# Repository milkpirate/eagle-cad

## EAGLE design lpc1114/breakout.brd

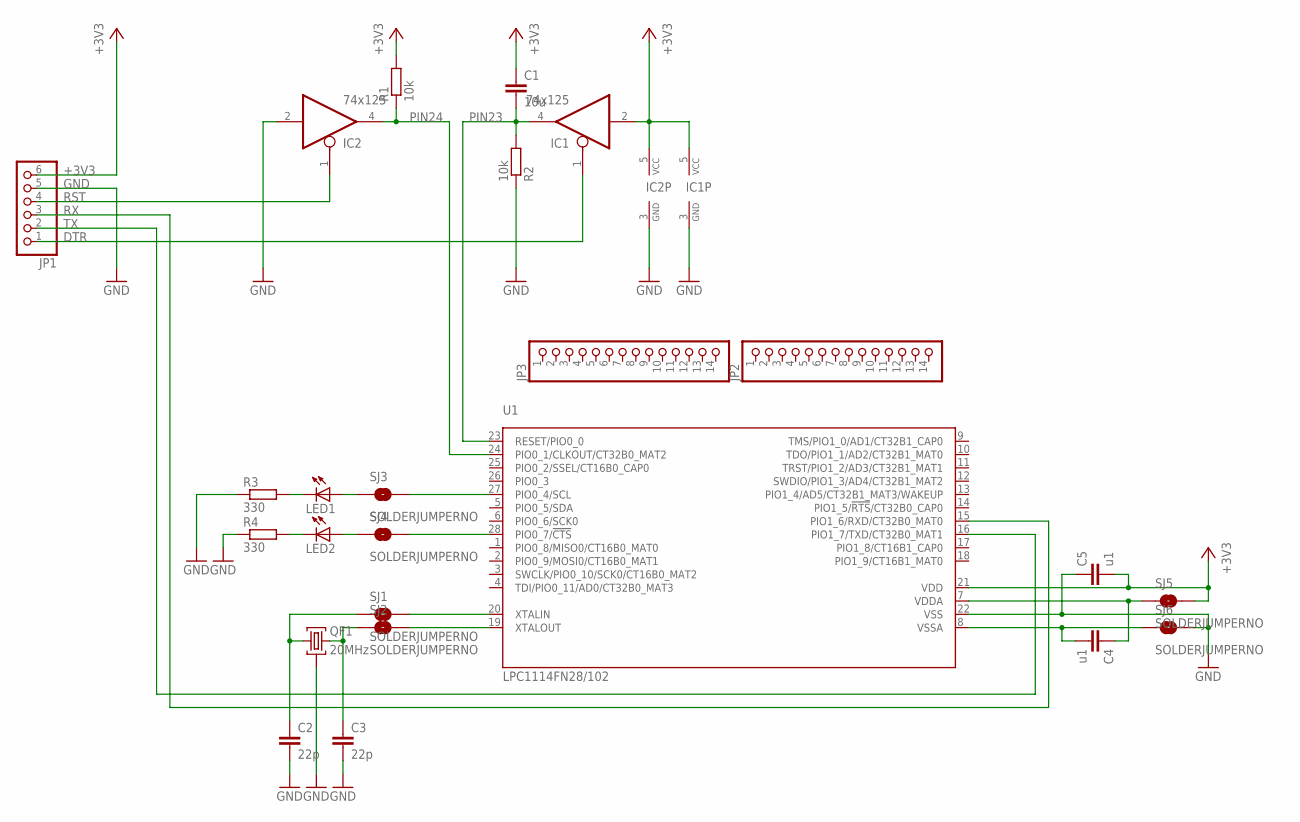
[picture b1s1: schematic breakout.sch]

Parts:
C1: 10u; C0805K
C2, C3: 22p; C0805K
C4, C5: u1; C0805K
IC1, IC2: 74x125; SOT23-5
JP1: PINHD-1X6/90; 1X06/90
JP2, JP3: PINHD-1X14; 1X14
LED1, LED2: LEDLD260; LD260
QF1: 20MHz; HC49U
R1, R2: 10k; M0805
R3, R4: 330; M0805
SJ1, SJ2, SJ3, SJ4, SJ5, SJ6: SOLDERJUMPERNO; SJ_2S-NO
U1: LPC1114FN28/102; SOT117

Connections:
+3V3: C1.1, C5.2, IC1.2 (I), IC1.5 (VCC), IC2.5 (VCC), JP1.6, R1.2, SJ5.2, U1.21 (VDD)
DTR: IC1.1 (OE), JP1.1
GND: C2.2, C3.2, C5.1, IC1.3 (GND), IC2.2 (I), IC2.3 (GND), JP1.5, QF1.2, R2.1, R3.1, R4.1, SJ6.2, U1.22 (VSS)
unnamed: LED2.A, SJ4.1
unnamed: LED1.A, SJ3.1
unnamed: LED1.K (C), R3.2
unnamed: LED2.K (C), R4.2
unnamed: SJ2.2, U1.19 (XTALOUT)
unnamed: SJ1.2, U1.20 (XTALIN)
unnamed: SJ4.2, U1.28 (PIO0_7/!CTS!)
unnamed: SJ3.2, U1.27 (PIO0_4/SCL)
unnamed: C3.1, QF1.3, SJ2.1
unnamed: C2.1, QF1.1, SJ1.1
PIN7: C4.1, SJ5.1, U1.7 (VDDA)
PIN8: C4.2, SJ6.1, U1.8 (VSSA)
PIN23: C1.2, IC1.4 (O), R2.2, U1.23 (RESET/PIO0_0)
PIN24: IC2.4 (O), R1.1, U1.24 (PIO0_1/CLKOUT/CT32B0_MAT2)
RST: IC2.1 (OE), JP1.4
RX: JP1.3, U1.15 (PIO1_6/RXD/CT32B0_MAT0)
TX: JP1.2, U1.16 (PIO1_7/TXD/CT32B0_MAT1)

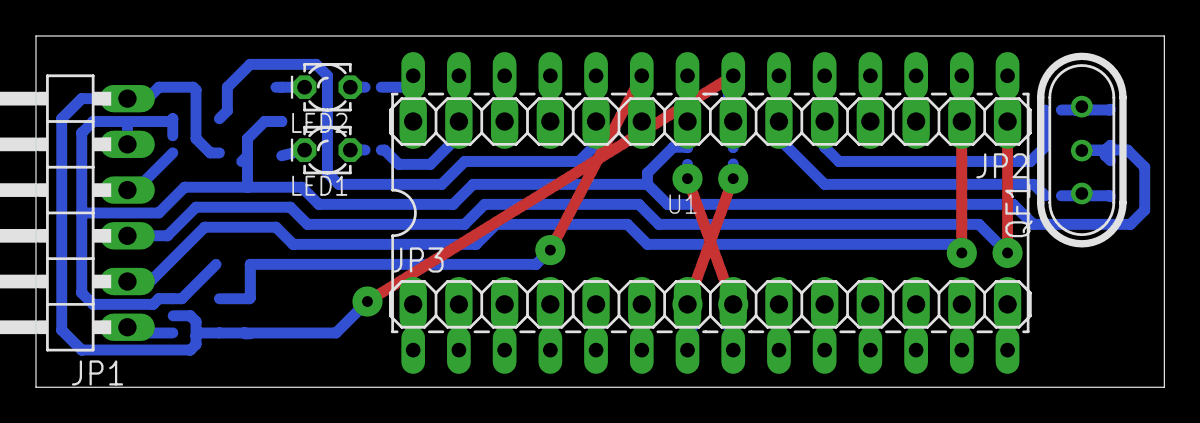
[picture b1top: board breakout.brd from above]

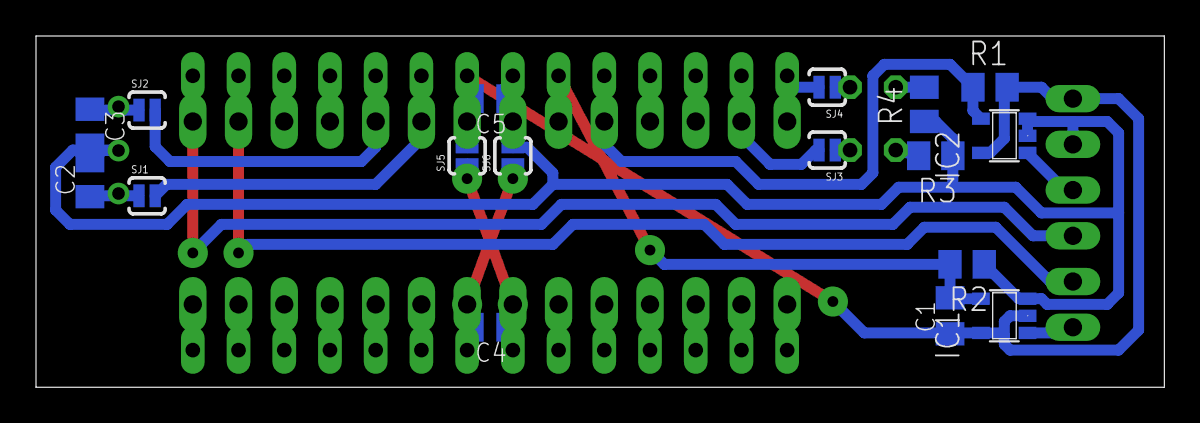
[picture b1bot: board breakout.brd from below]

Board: 2 copper layers, 62.7 x 19.5 mm, 24 parts (17 on the bottom side), 20 nets.

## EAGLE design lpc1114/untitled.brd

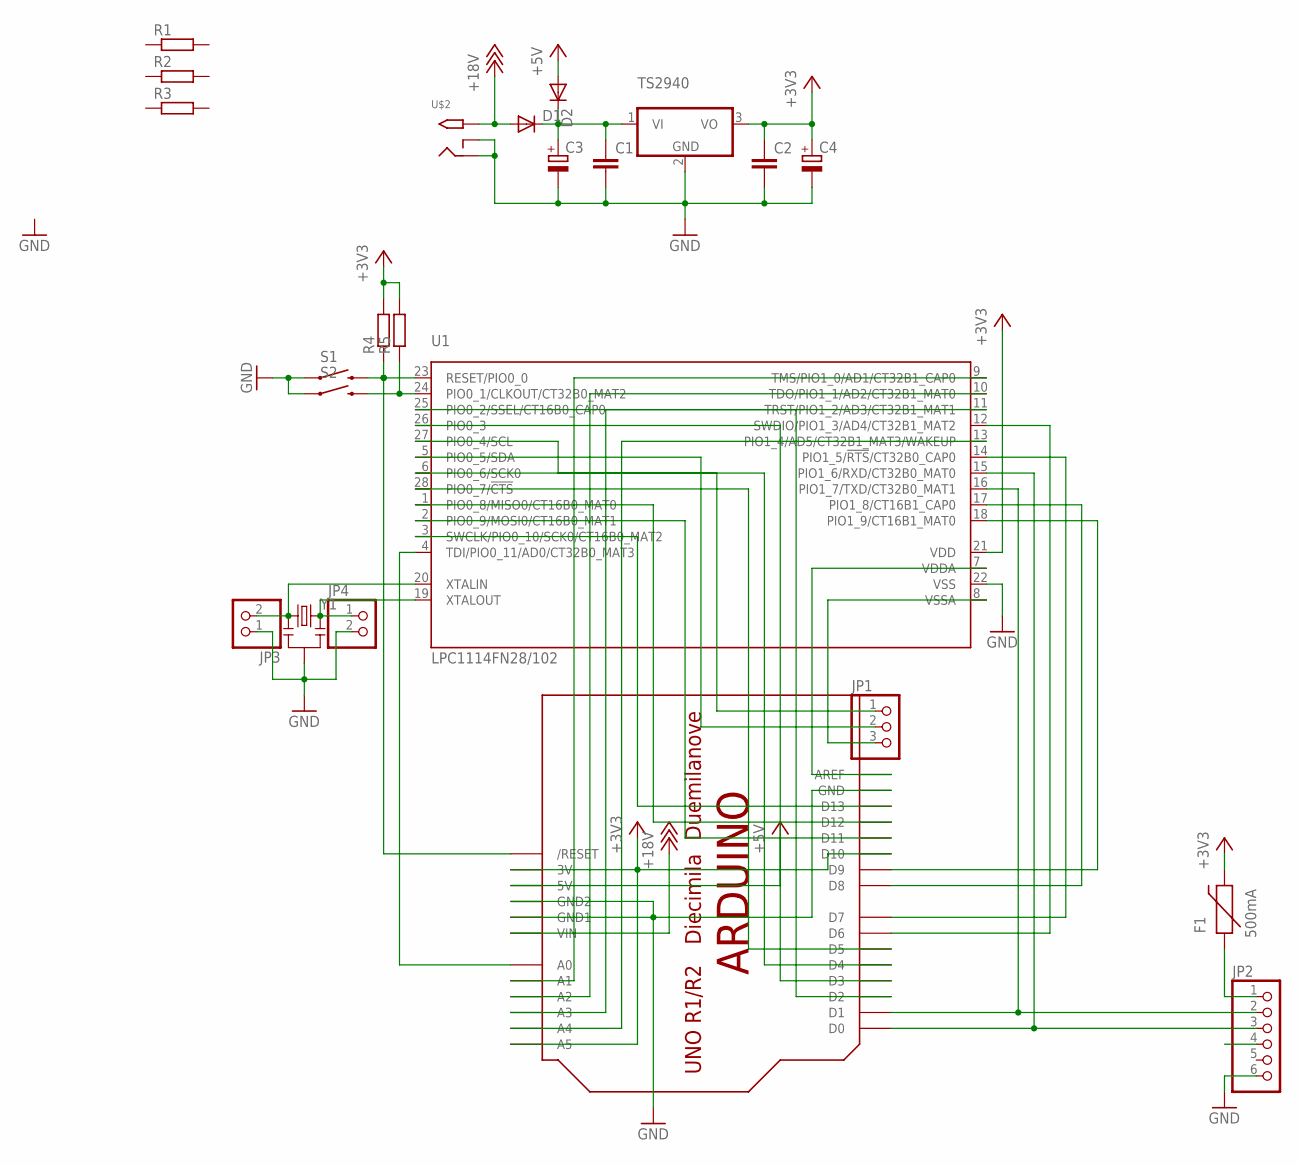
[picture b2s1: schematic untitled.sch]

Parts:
C1, C2: C-EU025-025X050; C025-025X050
C3, C4: CPOL-EUE2.5-6; E2,5-6
D1, D2: DIODE-C1702-05; C1702-05
F1: 500mA; PTC
JP1: PINHD-1X3; 1X03
JP2: PINHD-1X6/90; 1X06/90
JP3, JP4: PINHD-1X2; 1X02
R1, R2, R3, R4, R5: R-EU_0204/7; 0204/7
S1, S2: SWITCH-MOMENTARY-2PTH; TACTILE-PTH
TS2940: 7805T; TO220H
U1: LPC1114FN28/102; SOT117
U$1: ARDUINO-BPLACE
U$2: 2.1MMJACKTHM; PJ-102A
Y1: RESONATORPTH; RESONATOR-PTH

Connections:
+3V3: C2.1, C4.+, F1.P$2 (2), R4.2, R5.2, TS2940.3 (VO), U1.21 (VDD), U$1.3V, U$1.A5, U$1.D10
+5V: D2.A, U$1.5V
+18V: D1.A, U$1.VIN, U$2.TIP
GND: C1.2, C2.2, C3.-, C4.-, JP2.6, JP3.1, JP4.2, S1.1, S2.1, TS2940.2 (GND), U1.22 (VSS), U$1.GND, U$1.GND1, U$1.GND2, U$2.RING, U$2.RING_SW, Y1.2
unnamed: JP2.2, U1.16 (PIO1_7/TXD/CT32B0_MAT1), U$1.D1
unnamed: U1.4 (TDI/PIO0_11/AD0/CT32B0_MAT3), U$1.A0
unnamed: U1.9 (TMS/PIO1_0/AD1/CT32B1_CAP0), U$1.A1
unnamed: U1.10 (TDO/PIO1_1/AD2/CT32B1_MAT0), U$1.A2
unnamed: U1.11 (TRST/PIO1_2/AD3/CT32B1_MAT1), U$1.A3
unnamed: U1.13 (PIO1_4/AD5/CT32B1_MAT3/WAKEUP), U$1.A4
unnamed: C1.1, C3.+, D1.C, D2.C, TS2940.1 (VI)
unnamed: R4.1, S1.3 (2), U1.23 (RESET/PIO0_0), U$1.RESET (/RESET)
unnamed: U1.7 (VDDA), U$1.AREF
unnamed: JP1.3, U1.8 (VSSA)
unnamed: F1.P$1 (1), JP2.1
unnamed: U1.3 (SWCLK/PIO0_10/SCK0/CT16B0_MAT2), U$1.D13
unnamed: U1.2 (PIO0_9/MOSI0/CT16B0_MAT1), U$1.D11
unnamed: JP2.3, U1.15 (PIO1_6/RXD/CT32B0_MAT0), U$1.D0
unnamed: U1.1 (PIO0_8/MISO0/CT16B0_MAT0), U$1.D12
unnamed: JP1.2, U1.5 (PIO0_5/SDA)
unnamed: JP1.1, U1.27 (PIO0_4/SCL)
unnamed: R5.1, S2.3 (2), U1.24 (PIO0_1/CLKOUT/CT32B0_MAT2)
unnamed: JP3.2, U1.20 (XTALIN), Y1.1
unnamed: JP4.1, U1.19 (XTALOUT), Y1.3
unnamed: U1.25 (PIO0_2/SSEL/CT16B0_CAP0), U$1.D2
unnamed: U1.26 (PIO0_3), U$1.D3
unnamed: U1.6 (PIO0_6/SCK0), U$1.D4
unnamed: U1.28 (PIO0_7/!CTS!), U$1.D5
unnamed: U1.12 (SWDIO/PIO1_3/AD4/CT32B1_MAT2), U$1.D6
unnamed: U1.14 (PIO1_5/!RTS!/CT32B0_CAP0), U$1.D7
unnamed: U1.17 (PIO1_8/CT16B1_CAP0), U$1.D8
unnamed: U1.18 (PIO1_9/CT16B1_MAT0), U$1.D9

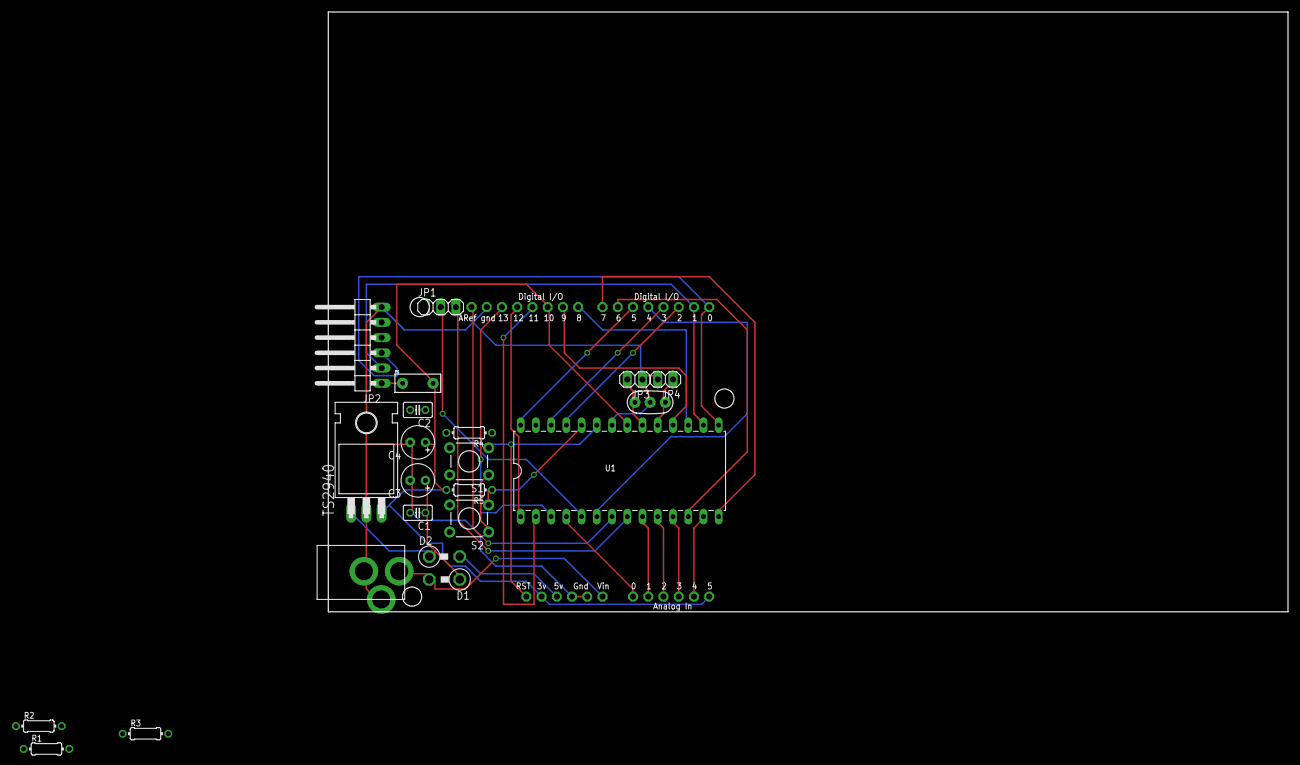
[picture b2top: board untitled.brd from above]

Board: 2 copper layers, 160.0 x 100.0 mm, 23 parts (0 on the bottom side), 32 nets.

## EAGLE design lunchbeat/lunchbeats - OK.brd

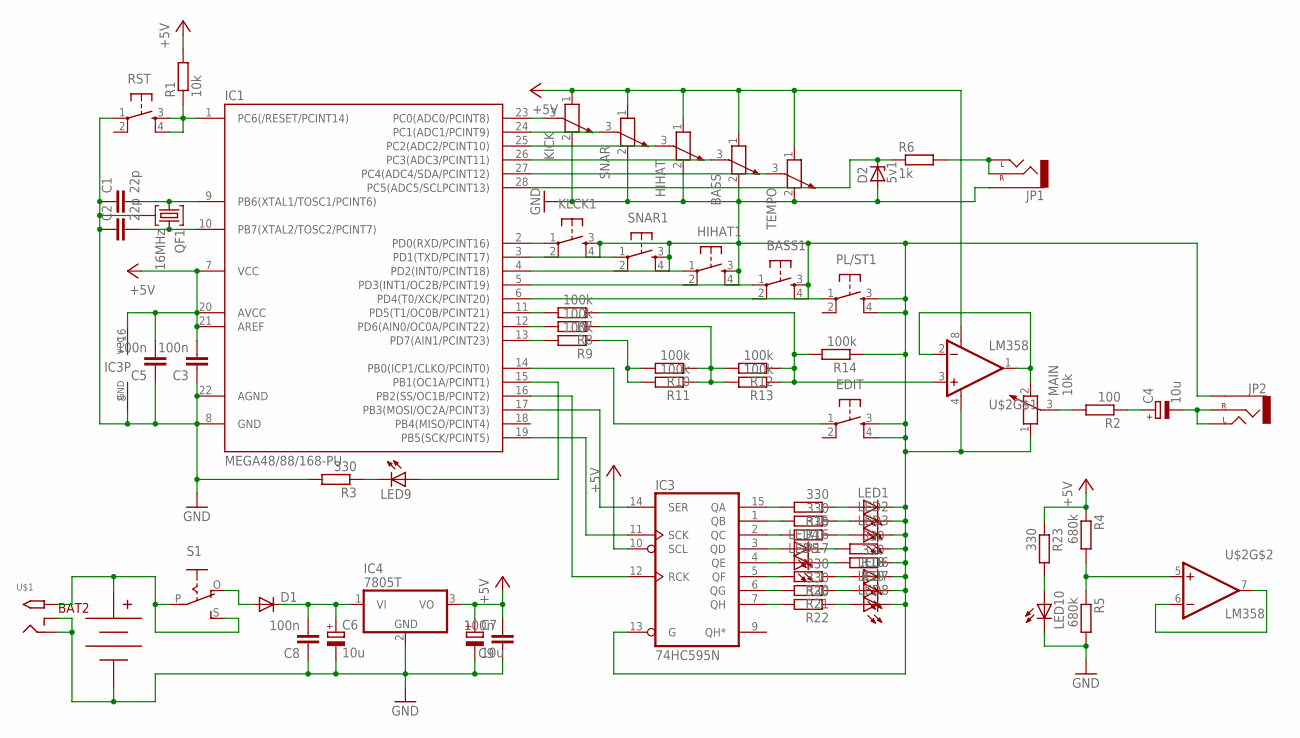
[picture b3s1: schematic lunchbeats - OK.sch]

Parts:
BASS: POTENTIOMETER_PT-10; PT-10
BASS1: TAC_SWITCHPTH; TACTILE-PTH
BAT2: BC9VPCKIT_SOLDERMASK; BC9VPC_KIT
C1, C2: 22p; C025-025X050
C3, C5, C8, C9: 100n; C025-025X050
C4: 10u; E2,5-6
C6, C7: 10u; E2,5-5
D1: DIODE-D-5; D-5
D2: 5v1; ZDIO-2.5
EDIT: TAC_SWITCHPTH; TACTILE-PTH
HIHAT: POTENTIOMETER_PT-10; PT-10
HIHAT1: TAC_SWITCHPTH; TACTILE-PTH
IC1: MEGA48/88/168-PU; DIL28-3
IC3: 74HC595N; DIL16
IC4: 7805T; TO220H
JP1, JP2: AUDIO-JACKPIN-HOLES; AUDIO-JACK-HOLES
KICK: POTENTIOMETER_PT-10; PT-10
KLCK1: TAC_SWITCHPTH; TACTILE-PTH
LED1, LED2, LED3, LED4, LED5, LED6, LED7, LED8, LED9, LED10: LED5MM
MAIN: 10k; PT-10
PL/ST1: TAC_SWITCHPTH; TACTILE-PTH
QF1: 16MHz; HC49U
R1: 10k; 0204/7
R2: 100; 0204/7
R3, R15, R16, R17, R18, R19, R20, R21, R22: 330; 0204/7
R4: 680k; 0204/5
R5: 680k; 0204/7
R6: 1k; 0204/7
R7, R8, R9, R10, R11, R12, R13, R14: 100k; 0204/7
R23: 330; 0204/5
RST: TAC_SWITCHPTH; TACTILE-PTH
S1: EG1218S; EG1218
SNAR: POTENTIOMETER_PT-10; PT-10
SNAR1: TAC_SWITCHPTH; TACTILE-PTH
TEMPO: POTENTIOMETER_PT-10; PT-10
U$1: 2.1MMJACKTHM; PJ-102A
U$2: LM358; DIP08

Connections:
+5V: BASS.1, C3.2, C5.2, C7.+, C9.2, HIHAT.1, IC1.7 (VCC), IC1.20 (AVCC), IC1.21 (AREF), IC3.10 (SCL), IC3.16 (VCC), IC4.3 (VO), KICK.1, R1.2, R4.1, R23.1, SNAR.1, TEMPO.1, U$2.8 (V+)
GND: BASS.2, BASS1.3, BASS1.4, BAT2.V+ (V-), C1.1, C2.1, C3.1, C5.1, C6.-, C7.-, C8.1, C9.1, D2.A, EDIT.3, EDIT.4, HIHAT.2, HIHAT1.3, HIHAT1.4, IC1.8 (GND), IC1.22 (AGND), IC3.8 (GND), IC3.13 (G), IC4.2 (GND), JP1.GND (SLEEVE), JP2.GND (SLEEVE), KICK.2, KLCK1.3, KLCK1.4, LED1.K (C), LED2.K (C), LED3.K (C), LED6.K (C), LED7.K (C), LED8.K (C), LED10.K (C), MAIN.1, PL/ST1.3, PL/ST1.4, QF1.2, R3.2, R5.2, R14.1, R18.1, R19.1, RST.1, SNAR.2, SNAR1.3, SNAR1.4, TEMPO.2, U$1.RING, U$1.RING_SW, U$2.4 (V-)
unnamed: C1.2, IC1.9 (PB6(XTAL1/TOSC1/PCINT6)), QF1.1
unnamed: C2.2, IC1.10 (PB7(XTAL2/TOSC2/PCINT7)), QF1.3
unnamed: IC1.2 (PD0(RXD/PCINT16)), KLCK1.1
unnamed: IC3.3 (QD), LED4.A
unnamed: IC1.1 (PC6(/RESET/PCINT14)), R1.1, RST.3, RST.4
unnamed: IC1.23 (PC0(ADC0/PCINT8)), KICK.3
unnamed: IC1.24 (PC1(ADC1/PCINT9)), SNAR.3
unnamed: HIHAT.3, IC1.25 (PC2(ADC2/PCINT10))
unnamed: BASS.3, IC1.26 (PC3(ADC3/PCINT11))
unnamed: IC1.27 (PC4(ADC4/SDA/PCINT12)), TEMPO.3
unnamed: LED4.K (C), R18.2
unnamed: IC3.4 (QE), LED5.A
unnamed: LED5.K (C), R19.2
unnamed: C4.-, JP2.L1- (LEFT), JP2.L2- (LEFT), JP2.R+ (RIGHT)
unnamed: IC1.11 (PD5(T1/OC0B/PCINT21)), R7.2
unnamed: IC1.12 (PD6(AIN0/OC0A/PCINT22)), R8.2
unnamed: IC1.13 (PD7(AIN1/PCINT23)), R9.2
unnamed: R9.1, R10.2, R11.2
unnamed: R8.1, R10.1, R11.1, R12.2, R13.2
unnamed: R7.1, R12.1, R13.1, R14.2, U$2.3 (+IN)
unnamed: EDIT.1, IC1.14 (PB0(ICP1/CLKO/PCINT0))
unnamed: MAIN.2, U$2.1 (OUT), U$2.2 (-IN)
unnamed: IC3.15 (QA), R15.2
unnamed: IC3.1 (QB), R16.2
unnamed: IC3.2 (QC), R17.2
unnamed: C4.+, R2.1
unnamed: MAIN.3, R2.2
unnamed: IC3.5 (QF), R20.2
unnamed: IC3.6 (QG), R21.2
unnamed: IC3.7 (QH), R22.2
unnamed: LED1.A, R15.1
unnamed: LED2.A, R16.1
unnamed: LED3.A, R17.1
unnamed: IC1.15 (PB1(OC1A/PCINT1)), LED9.A
unnamed: LED9.K (C), R3.1
unnamed: LED6.A, R20.1
unnamed: LED7.A, R21.1
unnamed: LED8.A, R22.1
unnamed: IC1.3 (PD1(TXD/PCINT17)), SNAR1.1
unnamed: HIHAT1.1, IC1.4 (PD2(INT0/PCINT18))
unnamed: IC1.17 (PB3(MOSI/OC2A/PCINT3)), IC3.14 (SER)
unnamed: IC1.19 (PB5(SCK/PCINT5)), IC3.11 (SCK)
unnamed: IC1.16 (PB2(SS/OC1B/PCINT2)), IC3.12 (RCK)
unnamed: BASS1.1, IC1.5 (PD3(INT1/OC2B/PCINT19))
unnamed: C6.+, C8.2, D1.C, IC4.1 (VI)
unnamed: BAT2.V- (V+), S1.P, S1.S, U$1.TIP
unnamed: D1.A, S1.O
unnamed: IC1.6 (PD4(T0/XCK/PCINT20)), PL/ST1.1
unnamed: JP1.L1- (LEFT), JP1.L2- (LEFT), JP1.R+ (RIGHT), R6.2
unnamed: R4.2, R5.1, U$2.5 (+IN)
unnamed: U$2.6 (-IN), U$2.7 (OUT)
unnamed: D2.C, IC1.28 (PC5(ADC5/SCLPCINT13)), R6.1
unnamed: LED10.A, R23.2

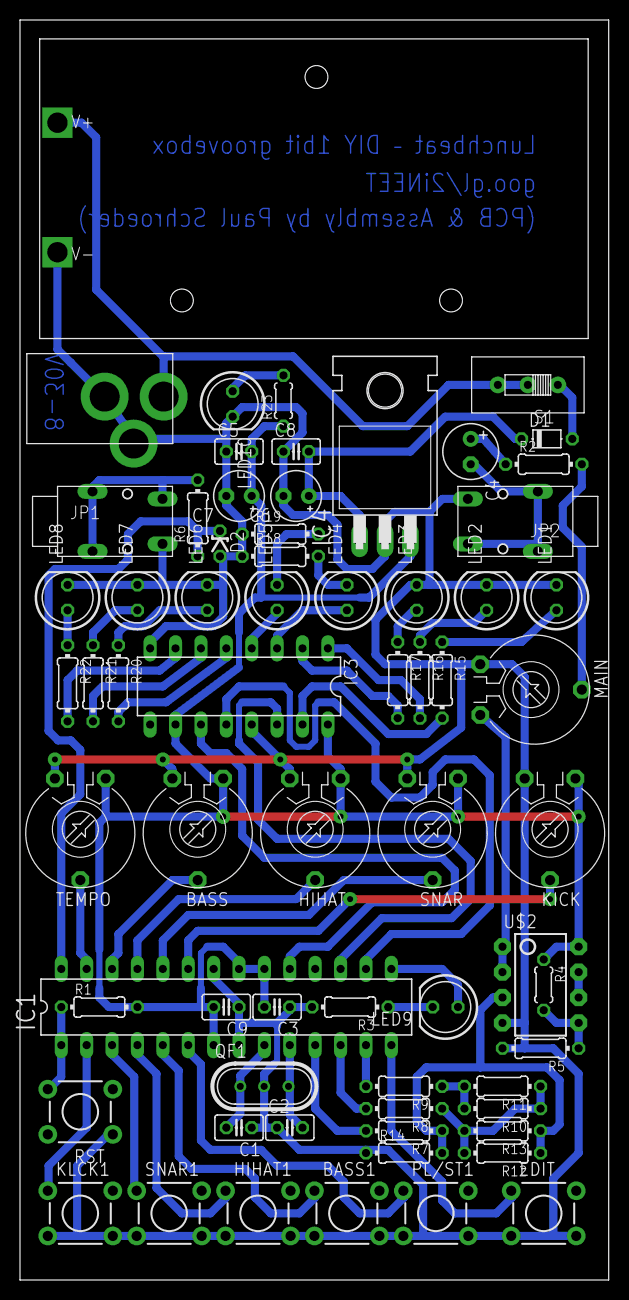
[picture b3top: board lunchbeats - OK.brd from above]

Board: 2 copper layers, 58.9 x 126.0 mm, 67 parts (0 on the bottom side), 55 nets.

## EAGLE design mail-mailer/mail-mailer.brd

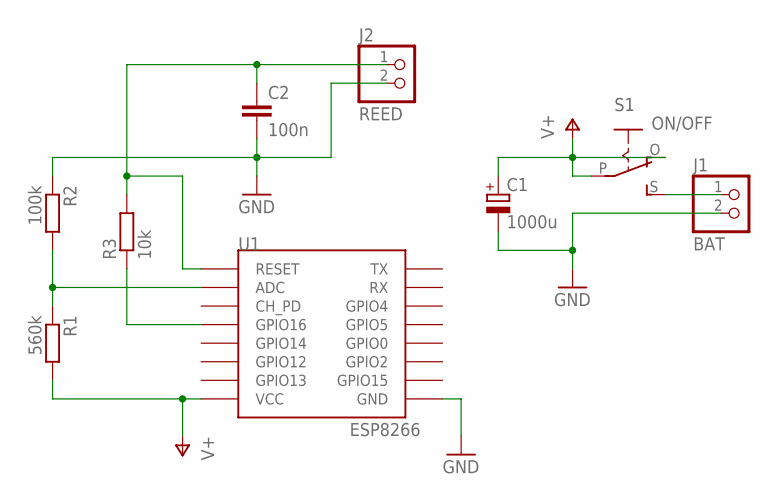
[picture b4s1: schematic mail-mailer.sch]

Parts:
C1: 1000u; E3,5-10
C2: 100n; C025-025X050
J1: BAT; 1X02
J2: REED; 1X02
R1: 560k; 0204/7
R2: 100k; 0204/7
R3: 10k; 0204/7
S1: ON/OFF; EG1218
U1: ESP8266; ESP-12-BREAKOUT

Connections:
GND: C1.-, C2.2, J1.2, J2.2, R2.1, U1.P$9 (GND)
J1: J1.1, S1.S
unnamed: R1.1, R2.2, U1.P$7 (ADC)
unnamed: R3.1, U1.P$5 (GPIO16)
unnamed: C2.1, J2.1, R3.2, U1.P$8 (RESET)
V+: C1.+, R1.2, S1.O, S1.P, U1.P$1 (VCC)

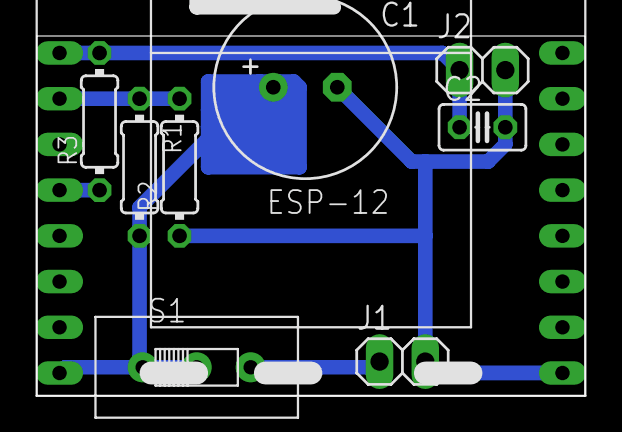
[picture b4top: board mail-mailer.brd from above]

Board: 2 copper layers, 30.5 x 20.0 mm, 9 parts (0 on the bottom side), 6 nets.

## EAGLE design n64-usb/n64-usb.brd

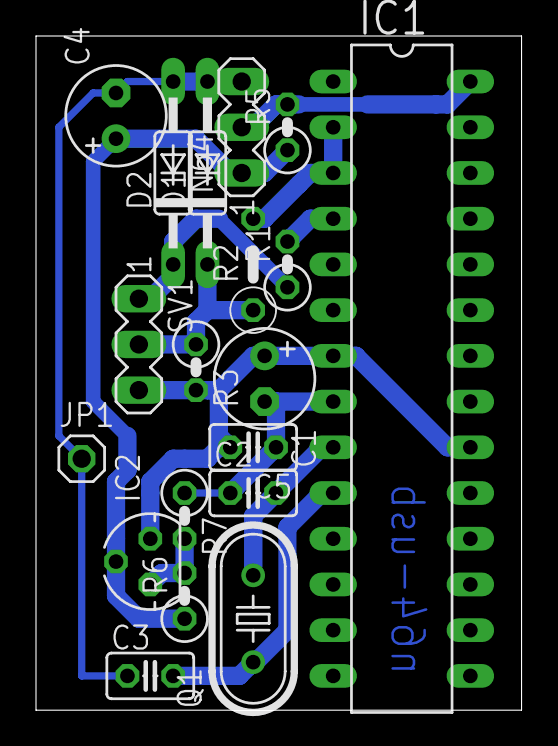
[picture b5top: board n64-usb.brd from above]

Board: 2 copper layers, 27.0 x 37.5 mm, 19 parts (0 on the bottom side), 11 nets.

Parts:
C1: 10u; E2,5-6
C2, C3: 27p; C025-025X050
C4: 22u; E2,5-6
C5: 100n; C025-025X050
D1, D2: 3V6; DO35-10
IC1: MEGA8-P; DIL28-3
IC2: LM317; 317L
JP1: 1X01
N64: MA03-1
Q1: 12Mhz; HC49U-V
R1: 68R; 0207/2V
R2: 68R; 0207/5V
R3: 1K5; 0207/2V
R5: 1K; 0207/2V
R6: 330R; 0207/2V
R7: 560R; 0207/2V
SV1: MA03-1

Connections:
+3V3: C4.+, IC2.2, N64.1, R5.1, R6.1
+5V: C1.+, C5.2, IC1.7, IC1.20, IC2.3, R3.2, SV1.3
DATA: IC1.28, N64.2, R5.2
GND: C1.-, C2.1, C3.1, C4.-, C5.1, D1.A, D2.A, IC1.8, IC1.22, JP1.1, N64.3, R7.1
unnamed: C3.2, IC1.10, Q1.1
unnamed: C2.2, IC1.9, Q1.2
unnamed: IC1.4, R1.2
unnamed: IC1.2, IC1.3, R2.2
unnamed: D2.C, R1.1, SV1.1
unnamed: D1.C, R2.1, R3.1, SV1.2
unnamed: IC2.1, R6.2, R7.2

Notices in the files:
parts and their libraries:
SparkFun-Passives: Licensing: CC v3.0 Share-Alike You are welcome to use this library for commercial purposes.
